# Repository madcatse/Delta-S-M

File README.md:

# Delta-S-M Ver.1.0 Gerber Files

Welcome to the first release of Gerber files for Delta-S-M Ver.1.0! This repository contains the manufacturing files necessary to produce the Delta-S-M Ver.1.0 board.

## Table of Contents
- [Introduction](#introduction)
- [Features](#features)
- [Getting Started](#getting-started)
- [Folder Structure](#folder-structure)
- [Cable pinout difference](#cable-pinout-difference)
- [Making SCART cable](#making-scart-cable)
- [License](#license)

## Introduction
Основной задачей данного проекта я поставил создание наиболее близкого к оригиналу клона персонального восьмибитного компьютера "Дельта-С", который в свою очередь является клоном ZX Spectrum 48K. Выбор модели был обусловлен давней мечтой об "улучшении" оригинальной машины, которой я обладаю с 1991 года. В процессе работы цель проекта несколько раз корректировалась и вместо точной копии стала некоторой "вариацией" на тему оригинала, с небольшими корректировками.

## Features
- High-performance microcontroller
- Multiple digital and analog I/O options
- Onboard peripherals such as LEDs, buttons, and connectors
- Expandable with additional modules or shields
- Compact form factor for easy integration

## Getting Started
To get started with Delta-S-M Ver.1.0, follow these steps:
1. Clone or download this repository.
2. Open the Gerber files in your preferred PCB manufacturing software.
3. Verify the design and make any necessary adjustments.
4. Generate the necessary manufacturing files (e.g., drill files, copper layers).
5. Submit the generated files to your preferred PCB manufacturer.
6. Review the manufacturer's guidelines and requirements for PCB production.
7. Proceed with the manufacturing process.
8. Once manufactured, assemble the components onto the PCB following the provided bill of materials (BOM).
9. Power up the Delta-S-M Ver.1.0 board and start exploring its capabilities!

## Folder Structure
The repository is organized as follows:
- /Gerber: Contains the Gerber files necessary for PCB manufacturing.
- /BOM: Includes the bill of materials (BOM) listing all components required for assembly.
- /Documentation: Provides additional documentation, schematics, and datasheets related to Delta-S-M Ver.1.0.

## Cable pinout difference

Be carefull, as there is a very important difference in video cable pinout between v0.1, v1.0 and v1.2 and up.

**v0.1 and v1.0 boards video pinout:**

- 1 - Sync
- 2 - Red
- 3 - N/C
- 4 - Blue
- 5 - Green
- 6 - GND
- 7 - +5V

**v1.2 boards video pinout:**

- 1 - Sync
- 2 - GND
- 3 - Red
- 4 - Green
- 5 - Blue
- 6 - Audio
- 7 - +5V

V1.2 boards are compatible with original Delta-S and Delta-128 and could be connected with their cables.

## Making SCART cable
The best video quality could be achived with SCART cable with RGB mode. Delta S-M is capable of outputting native RGB signal and uses a SCART cable to connect to RGB-capable TVs. The picture below illustrates pinout of both SCART plug and DIN-7 plug.

SCART Pinout

15 - Red
11 - Green
7 - Blue
20 - Sync
16 - ADD 180 Ohm resistor between computer and SCART plug and connect it to pin 16 to enable switching to correct RGB mode. Direct +5V could DAMAGE YOUR TV!
5, 9, 13, 17 and 21 (metal case) - Ground

## License
This project is licensed under the [MIT License](LICENSE). Feel free to use, modify, and distribute the Delta-S-M Ver.1.0 Gerber files as per the terms of the license.

For more details, refer to the [LICENSE](LICENSE) file.

---

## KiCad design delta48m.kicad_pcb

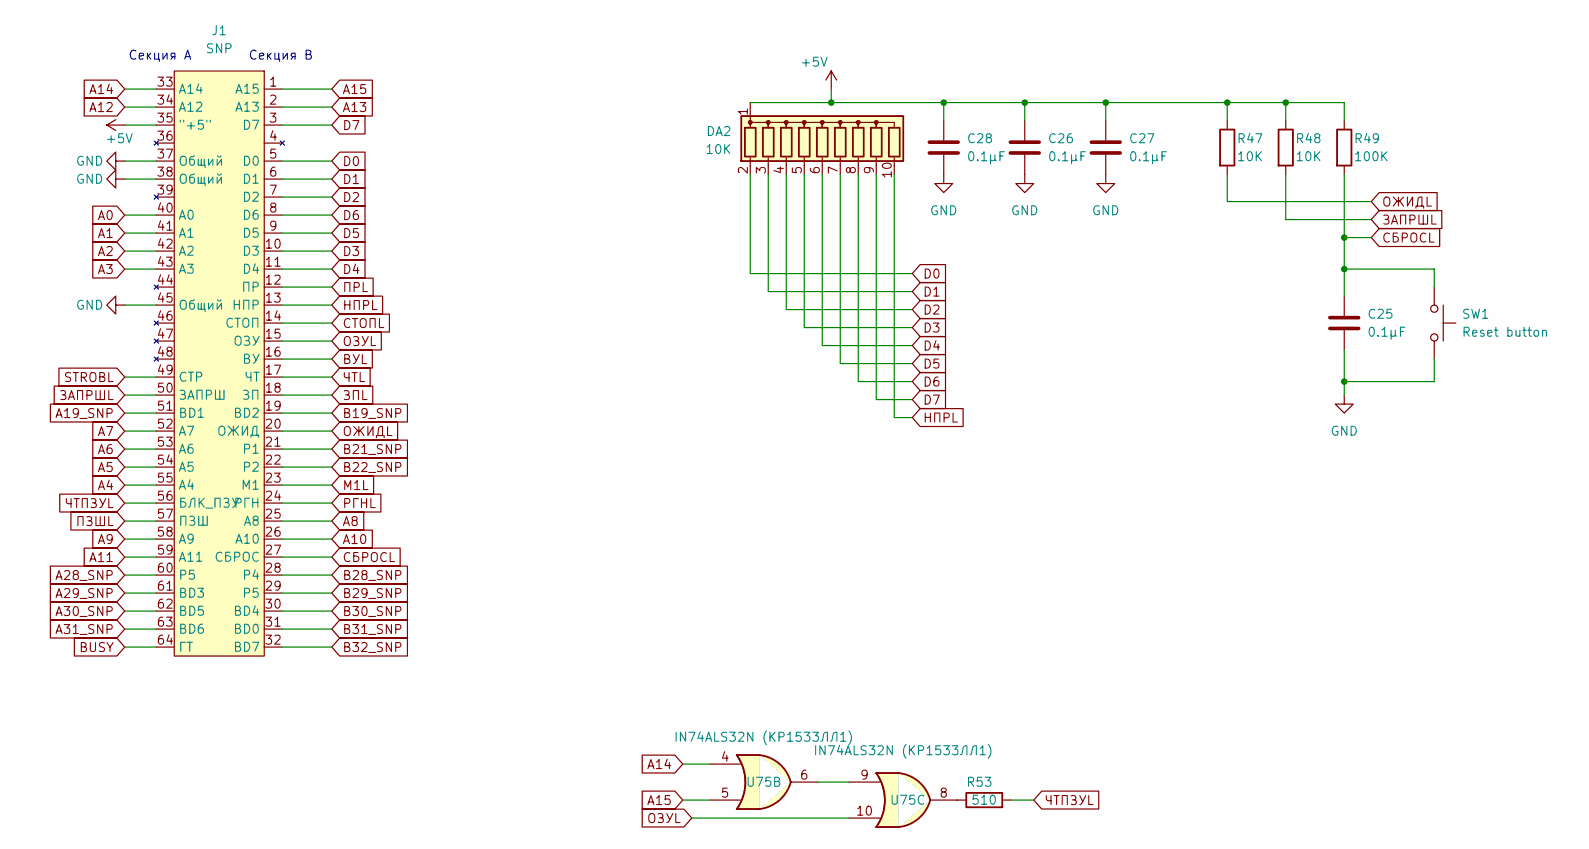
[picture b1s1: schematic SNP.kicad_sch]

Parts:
C25, C26, C27, C28: 0.1μF; C_Disc_D7.0mm_W2.5mm_P5.00mm
DA2: 10K; R_Array_SIP10
J1: SNP; snp59_96_female_angle_3
R47, R48: 10K; R_Axial_DIN0207_L6.3mm_D2.5mm_P10.16mm_Horizontal
R49: 100K; R_Axial_DIN0207_L6.3mm_D2.5mm_P10.16mm_Horizontal
R53: 510; R_Axial_DIN0207_L6.3mm_D2.5mm_P10.16mm_Horizontal
SW1: Reset button; SW_Tactile_SPST_Angled_PTS645Vx83-2LFS
U75: IN74ALS32N (КР1533ЛЛ1); DIP-14_W7.62mm_Socket

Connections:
+5V: C26.1, C27.1, C28.1, DA2.1 (common), J1.35 ("+5"), R47.1, R48.1, R49.1; also elsewhere on the board
A0: J1.40 (A0); also elsewhere on the board
A1: J1.41 (A1); also elsewhere on the board
A2: J1.42 (A2); also elsewhere on the board
A3: J1.43 (A3); also elsewhere on the board
A4: J1.55 (A4); also elsewhere on the board
A5: J1.54 (A5); also elsewhere on the board
A6: J1.53 (A6); also elsewhere on the board
A7: J1.52 (A7); also elsewhere on the board
A8: J1.25 (A8); also elsewhere on the board
A9: J1.58 (A9); also elsewhere on the board
A10: J1.26 (A10); also elsewhere on the board
A11: J1.59 (A11); also elsewhere on the board
A12: J1.34 (A12); also elsewhere on the board
A13: J1.2 (A13); also elsewhere on the board
A14: J1.33 (A14), U75.4; also elsewhere on the board
A15: J1.1 (A15), U75.5; also elsewhere on the board
A19_SNP: J1.51 (BD1); also elsewhere on the board
A28_SNP: J1.60 (P5); also elsewhere on the board
A29_SNP: J1.61 (BD3); also elsewhere on the board
A30_SNP: J1.62 (BD5); also elsewhere on the board
A31_SNP: J1.63 (BD6); also elsewhere on the board
B19_SNP: J1.19 (BD2); also elsewhere on the board
B21_SNP: J1.21 (P1); also elsewhere on the board
B22_SNP: J1.22 (P2); also elsewhere on the board
B28_SNP: J1.28 (P4); also elsewhere on the board
B29_SNP: J1.29 (P5); also elsewhere on the board
B30_SNP: J1.30 (BD4); also elsewhere on the board
B31_SNP: J1.31 (BD0); also elsewhere on the board
B32_SNP: J1.32 (BD7); also elsewhere on the board
BUSY: J1.64 (ГТ); also elsewhere on the board
D0: DA2.2 (R1), J1.5 (D0); also elsewhere on the board
D1: DA2.3 (R2), J1.6 (D1); also elsewhere on the board
D2: DA2.4 (R3), J1.7 (D2); also elsewhere on the board
D3: DA2.5 (R4), J1.10 (D3); also elsewhere on the board
D4: DA2.6 (R5), J1.11 (D4); also elsewhere on the board
D5: DA2.7 (R6), J1.9 (D5); also elsewhere on the board
D6: DA2.8 (R7), J1.8 (D6); also elsewhere on the board
D7: DA2.9 (R8), J1.3 (D7); also elsewhere on the board
GND: C25.2, C26.2, C27.2, C28.2, J1.37 (Общий), J1.38 (Общий), J1.45 (Общий), SW1.2; also elsewhere on the board
M1L: J1.23 (М1); also elsewhere on the board
unnamed: R53.1, U75.8
unnamed: U75.6, U75.9
STROBL: J1.49 (СТР); also elsewhere on the board
ВУL: J1.16 (ВУ); also elsewhere on the board
ЗАПРШL: J1.50 (ЗАПРШ), R48.2; also elsewhere on the board
ЗПL: J1.18 (ЗП); also elsewhere on the board
НПРL: DA2.10 (R9), J1.13 (НПР); also elsewhere on the board
ОЖИДL: J1.20 (ОЖИД), R47.2; also elsewhere on the board
ОЗУL: J1.15 (ОЗУ), U75.10; also elsewhere on the board
ПЗШL: J1.57 (ПЗШ); also elsewhere on the board
ПРL: J1.12 (ПР); also elsewhere on the board
РГНL: J1.24 (РГН); also elsewhere on the board
СБРОСL: C25.1, J1.27 (СБРОС), R49.2, SW1.1; also elsewhere on the board
СТОПL: J1.14 (СТОП); also elsewhere on the board
ЧТL: J1.17 (ЧТ); also elsewhere on the board
ЧТПЗУL: J1.56 (БЛК_ПЗУ), R53.2; also elsewhere on the board

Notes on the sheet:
Секция А
Секция В

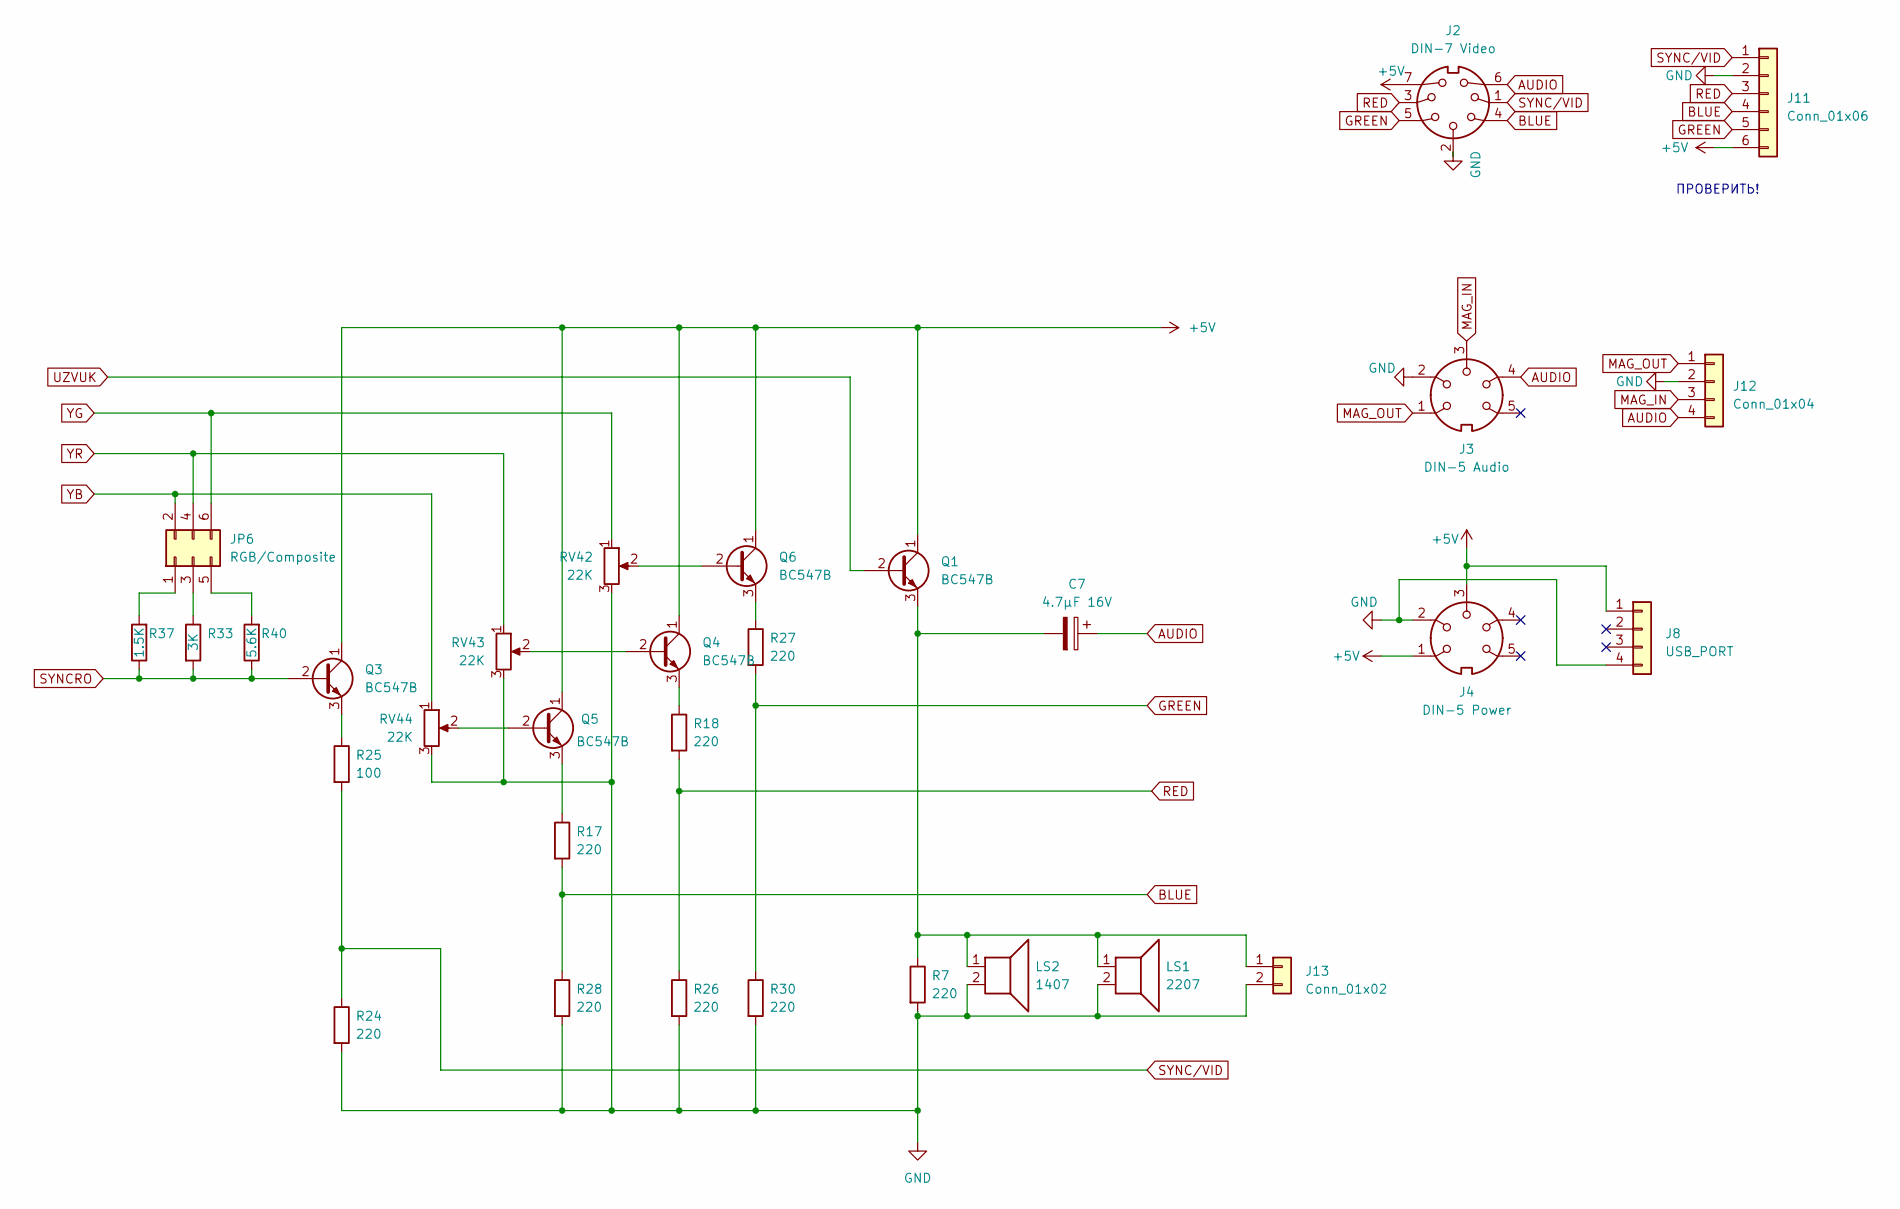
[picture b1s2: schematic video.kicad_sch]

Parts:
C7: 4.7µF 16V; CP_Radial_D4.0mm_P2.00mm
J2: DIN-7 Video; DIN-7-Variable
J3: DIN-5 Audio; DIN-5-Variable
J4: DIN-5 Power; DIN-5-Variable
J8: USB_PORT; USB-C Power board
J11: Conn_01x06; PinHeader_1x06_P2.54mm_Vertical
J12: Conn_01x04; PinHeader_1x04_P2.54mm_Vertical
J13: Conn_01x02; PinHeader_1x02_P2.54mm_Vertical
JP6: RGB/Composite; PinHeader_2x03_P2.54mm_Vertical
LS1: 2207; ZM-Piezo Buzzer-2207T2
LS2: 1407; 1407 Piezoelectric Passive Buzzer
Q1, Q3, Q4, Q5, Q6: BC547B; TO-92_Inline
R7, R17, R18, R24, R26, R27, R28, R30: 220; R_Axial_DIN0207_L6.3mm_D2.5mm_P10.16mm_Horizontal
R25: 100; R_Axial_DIN0207_L6.3mm_D2.5mm_P10.16mm_Horizontal
R33: 3K; R_Axial_DIN0207_L6.3mm_D2.5mm_P10.16mm_Horizontal
R37: 1.5K; R_Axial_DIN0207_L6.3mm_D2.5mm_P10.16mm_Horizontal
R40: 5.6K; R_Axial_DIN0207_L6.3mm_D2.5mm_P10.16mm_Horizontal
RV42, RV43, RV44: 22K; Potentiometer_Bourns_3299X_Horizontal

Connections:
+5V: J2.7, J4.1, J4.3, J8.1, J11.6, Q1.1 (C), Q3.1 (C), Q4.1 (C), Q5.1 (C), Q6.1 (C); also elsewhere on the board
AUDIO: C7.1, J2.6, J3.4, J12.4
BLUE: J2.4, J11.4, R17.2, R28.1
GND: J2.2, J3.2, J4.2, J8.4, J11.2, J12.2, J13.2, LS1.2, LS2.2, R7.2, R24.2, R26.2, R28.2, R30.2, RV42.3, RV43.3, RV44.3; also elsewhere on the board
GREEN: J2.5, J11.5, R27.2, R30.1
MAG_IN: J3.3, J12.3; also elsewhere on the board
MAG_OUT: J3.1, J12.1; also elsewhere on the board
unnamed: C7.2, J13.1, LS1.1, LS2.1, Q1.3 (E), R7.1
unnamed: JP6.1, R37.2
unnamed: JP6.3, R33.1
unnamed: JP6.5, R40.2
unnamed: Q3.3 (E), R25.1
unnamed: Q4.2 (B), RV43.2
unnamed: Q4.3 (E), R18.1
unnamed: Q5.2 (B), RV44.2
unnamed: Q5.3 (E), R17.1
unnamed: Q6.2 (B), RV42.2
unnamed: Q6.3 (E), R27.1
RED: J2.3, J11.3, R18.2, R26.1
SYNCRO: Q3.2 (B), R33.2, R37.1, R40.1; also elsewhere on the board
SYNC/VID: J2.1, J11.1, R24.1, R25.2
UZVUK: Q1.2 (B); also elsewhere on the board
YB: JP6.2, RV44.1; also elsewhere on the board
YG: JP6.6, RV42.1; also elsewhere on the board
YR: JP6.4, RV43.1; also elsewhere on the board

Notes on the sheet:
ПРОВЕРИТЬ!

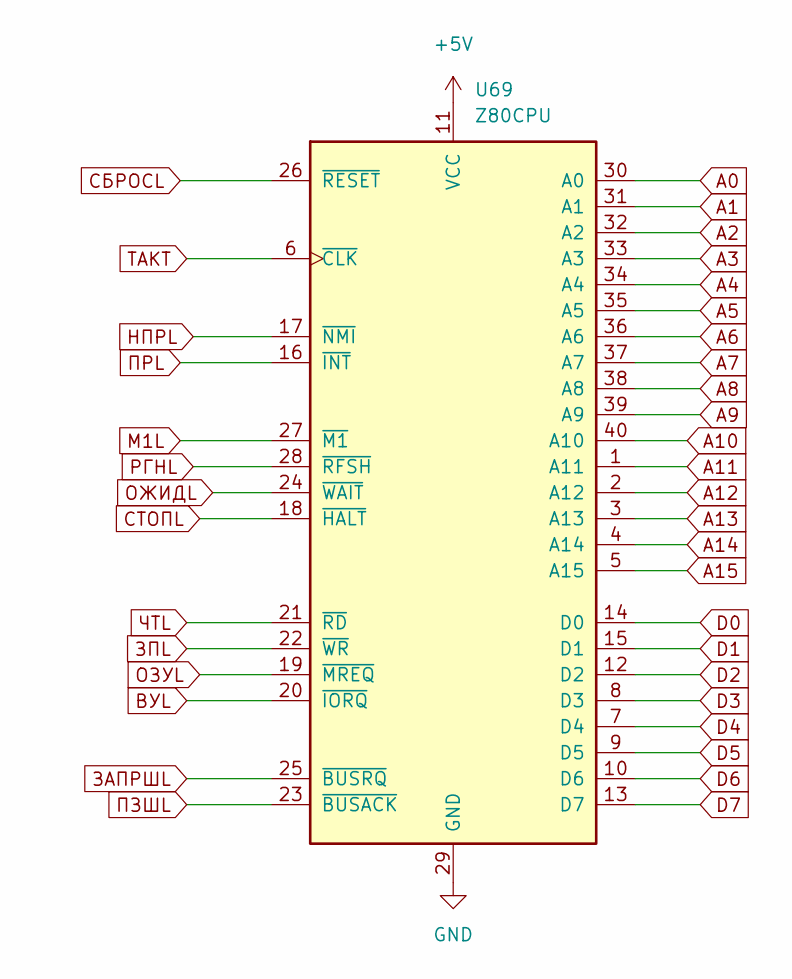
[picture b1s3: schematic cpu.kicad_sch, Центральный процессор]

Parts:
U69: Z80CPU; DIP-40_W15.24mm_Socket

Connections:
+5V: U69.11 (VCC); also elsewhere on the board
A0: U69.30 (A0); also elsewhere on the board
A1: U69.31 (A1); also elsewhere on the board
A2: U69.32 (A2); also elsewhere on the board
A3: U69.33 (A3); also elsewhere on the board
A4: U69.34 (A4); also elsewhere on the board
A5: U69.35 (A5); also elsewhere on the board
A6: U69.36 (A6); also elsewhere on the board
A7: U69.37 (A7); also elsewhere on the board
A8: U69.38 (A8); also elsewhere on the board
A9: U69.39 (A9); also elsewhere on the board
A10: U69.40 (A10); also elsewhere on the board
A11: U69.1 (A11); also elsewhere on the board
A12: U69.2 (A12); also elsewhere on the board
A13: U69.3 (A13); also elsewhere on the board
A14: U69.4 (A14); also elsewhere on the board
A15: U69.5 (A15); also elsewhere on the board
D0: U69.14 (D0); also elsewhere on the board
D1: U69.15 (D1); also elsewhere on the board
D2: U69.12 (D2); also elsewhere on the board
D3: U69.8 (D3); also elsewhere on the board
D4: U69.7 (D4); also elsewhere on the board
D5: U69.9 (D5); also elsewhere on the board
D6: U69.10 (D6); also elsewhere on the board
D7: U69.13 (D7); also elsewhere on the board
GND: U69.29 (GND); also elsewhere on the board
M1L: U69.27 (~M1); also elsewhere on the board
ВУL: U69.20 (~IORQ); also elsewhere on the board
ЗАПРШL: U69.25 (~BUSRQ); also elsewhere on the board
ЗПL: U69.22 (~WR); also elsewhere on the board
НПРL: U69.17 (~NMI); also elsewhere on the board
ОЖИДL: U69.24 (~WAIT); also elsewhere on the board
ОЗУL: U69.19 (~MREQ); also elsewhere on the board
ПЗШL: U69.23 (~BUSACK); also elsewhere on the board
ПРL: U69.16 (~INT); also elsewhere on the board
РГНL: U69.28 (~RFSH); also elsewhere on the board
СБРОСL: U69.26 (~RESET); also elsewhere on the board
СТОПL: U69.18 (~HALT); also elsewhere on the board
ТАКТ: U69.6 (~CLK); also elsewhere on the board
ЧТL: U69.21 (~RD); also elsewhere on the board

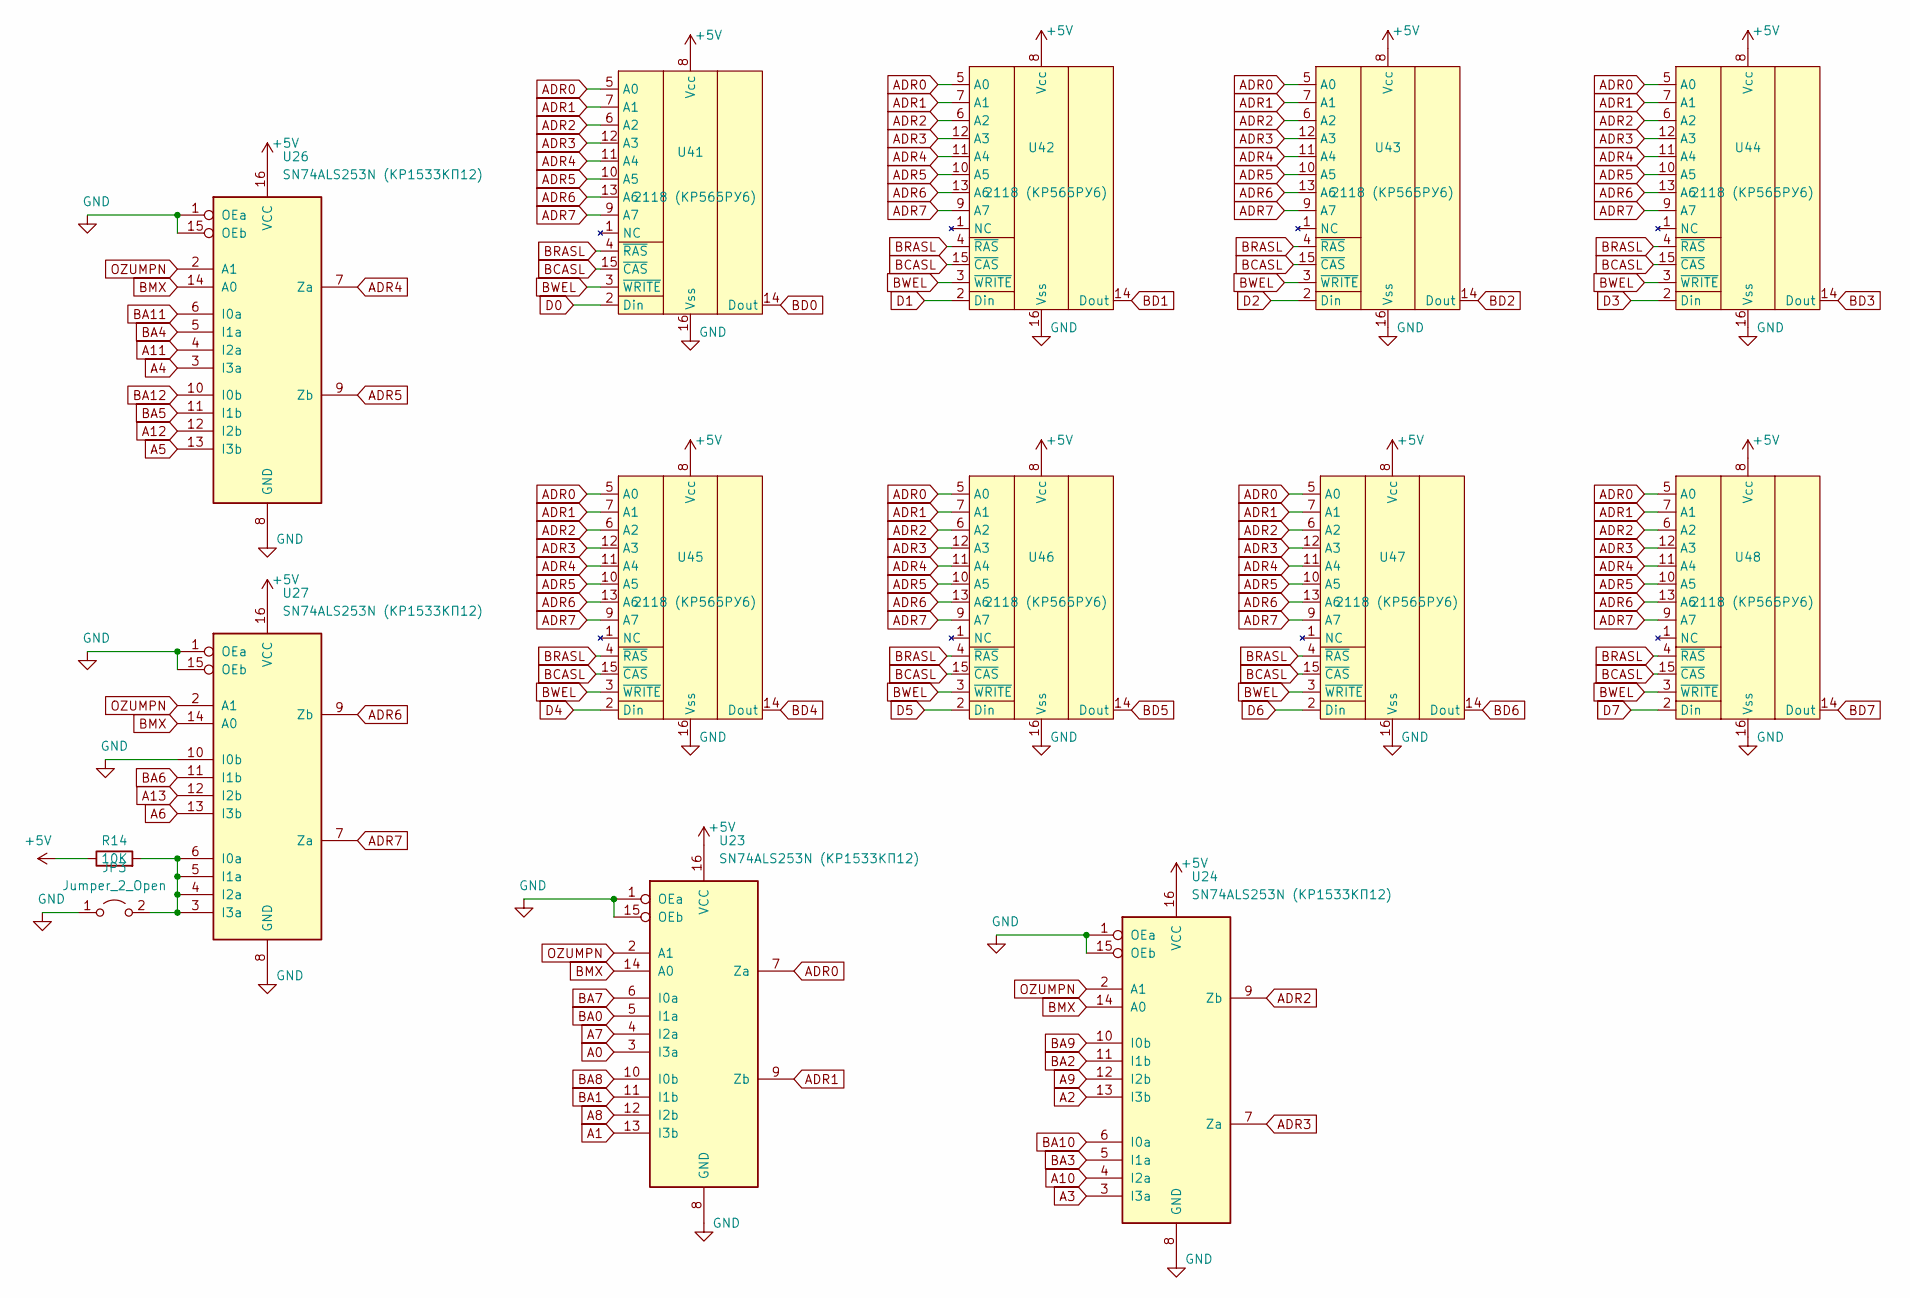
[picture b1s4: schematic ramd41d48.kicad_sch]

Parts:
JP3: Jumper_2_Open; PinHeader_1x02_P2.54mm_Vertical
R14: 10K; R_Axial_DIN0207_L6.3mm_D2.5mm_P10.16mm_Horizontal
U23, U24, U26, U27: SN74ALS253N (КР1533КП12); DIP-16_W7.62mm_Socket
U41, U42, U43, U44, U45, U46, U47, U48: 2118 (КР565РУ6); DIP-16_W7.62mm_Socket

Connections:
+5V: R14.1, U23.16 (VCC), U24.16 (VCC), U26.16 (VCC), U27.16 (VCC), U41.8 (Vcc), U42.8 (Vcc), U43.8 (Vcc), U44.8 (Vcc), U45.8 (Vcc), U46.8 (Vcc), U47.8 (Vcc), U48.8 (Vcc); also elsewhere on the board
A0: U23.3 (I3a); also elsewhere on the board
A1: U23.13 (I3b); also elsewhere on the board
A2: U24.13 (I3b); also elsewhere on the board
A3: U24.3 (I3a); also elsewhere on the board
A4: U26.3 (I3a); also elsewhere on the board
A5: U26.13 (I3b); also elsewhere on the board
A6: U27.13 (I3b); also elsewhere on the board
A7: U23.4 (I2a); also elsewhere on the board
A8: U23.12 (I2b); also elsewhere on the board
A9: U24.12 (I2b); also elsewhere on the board
A10: U24.4 (I2a); also elsewhere on the board
A11: U26.4 (I2a); also elsewhere on the board
A12: U26.12 (I2b); also elsewhere on the board
A13: U27.12 (I2b); also elsewhere on the board
ADR0: U23.7 (Za), U41.5 (A0), U42.5 (A0), U43.5 (A0), U44.5 (A0), U45.5 (A0), U46.5 (A0), U47.5 (A0), U48.5 (A0)
ADR1: U23.9 (Zb), U41.7 (A1), U42.7 (A1), U43.7 (A1), U44.7 (A1), U45.7 (A1), U46.7 (A1), U47.7 (A1), U48.7 (A1)
ADR2: U24.9 (Zb), U41.6 (A2), U42.6 (A2), U43.6 (A2), U44.6 (A2), U45.6 (A2), U46.6 (A2), U47.6 (A2), U48.6 (A2)
ADR3: U24.7 (Za), U41.12 (A3), U42.12 (A3), U43.12 (A3), U44.12 (A3), U45.12 (A3), U46.12 (A3), U47.12 (A3), U48.12 (A3)
ADR4: U26.7 (Za), U41.11 (A4), U42.11 (A4), U43.11 (A4), U44.11 (A4), U45.11 (A4), U46.11 (A4), U47.11 (A4), U48.11 (A4)
ADR5: U26.9 (Zb), U41.10 (A5), U42.10 (A5), U43.10 (A5), U44.10 (A5), U45.10 (A5), U46.10 (A5), U47.10 (A5), U48.10 (A5)
ADR6: U27.9 (Zb), U41.13 (A6), U42.13 (A6), U43.13 (A6), U44.13 (A6), U45.13 (A6), U46.13 (A6), U47.13 (A6), U48.13 (A6)
ADR7: U27.7 (Za), U41.9 (A7), U42.9 (A7), U43.9 (A7), U44.9 (A7), U45.9 (A7), U46.9 (A7), U47.9 (A7), U48.9 (A7)
BA0: U23.5 (I1a); also elsewhere on the board
BA1: U23.11 (I1b); also elsewhere on the board
BA2: U24.11 (I1b); also elsewhere on the board
BA3: U24.5 (I1a); also elsewhere on the board
BA4: U26.5 (I1a); also elsewhere on the board
BA5: U26.11 (I1b); also elsewhere on the board
BA6: U27.11 (I1b); also elsewhere on the board
BA7: U23.6 (I0a); also elsewhere on the board
BA8: U23.10 (I0b); also elsewhere on the board
BA9: U24.10 (I0b); also elsewhere on the board
BA10: U24.6 (I0a); also elsewhere on the board
BA11: U26.6 (I0a); also elsewhere on the board
BA12: U26.10 (I0b); also elsewhere on the board
BCASL: U41.15 (~CAS), U42.15 (~CAS), U43.15 (~CAS), U44.15 (~CAS), U45.15 (~CAS), U46.15 (~CAS), U47.15 (~CAS), U48.15 (~CAS); also elsewhere on the board
BD0: U41.14 (Dout); also elsewhere on the board
BD1: U42.14 (Dout); also elsewhere on the board
BD2: U43.14 (Dout); also elsewhere on the board
BD3: U44.14 (Dout); also elsewhere on the board
BD4: U45.14 (Dout); also elsewhere on the board
BD5: U46.14 (Dout); also elsewhere on the board
BD6: U47.14 (Dout); also elsewhere on the board
BD7: U48.14 (Dout); also elsewhere on the board
BMX: U23.14 (A0), U24.14 (A0), U26.14 (A0), U27.14 (A0); also elsewhere on the board
BRASL: U41.4 (~RAS), U42.4 (~RAS), U43.4 (~RAS), U44.4 (~RAS), U45.4 (~RAS), U46.4 (~RAS), U47.4 (~RAS), U48.4 (~RAS); also elsewhere on the board
BWEL: U41.3 (~WRITE), U42.3 (~WRITE), U43.3 (~WRITE), U44.3 (~WRITE), U45.3 (~WRITE), U46.3 (~WRITE), U47.3 (~WRITE), U48.3 (~WRITE); also elsewhere on the board
D0: U41.2 (Din); also elsewhere on the board
D1: U42.2 (Din); also elsewhere on the board
D2: U43.2 (Din); also elsewhere on the board
D3: U44.2 (Din); also elsewhere on the board
D4: U45.2 (Din); also elsewhere on the board
D5: U46.2 (Din); also elsewhere on the board
D6: U47.2 (Din); also elsewhere on the board
D7: U48.2 (Din); also elsewhere on the board
GND: JP3.1 (A), U23.1 (OEa), U23.8 (GND), U23.15 (OEb), U24.1 (OEa), U24.8 (GND), U24.15 (OEb), U26.1 (OEa), U26.8 (GND), U26.15 (OEb), U27.1 (OEa), U27.8 (GND), U27.10 (I0b), U27.15 (OEb), U41.16 (Vss), U42.16 (Vss), U43.16 (Vss), U44.16 (Vss), U45.16 (Vss), U46.16 (Vss), U47.16 (Vss), U48.16 (Vss); also elsewhere on the board
unnamed: JP3.2 (B), R14.2, U27.3 (I3a), U27.4 (I2a), U27.5 (I1a), U27.6 (I0a)
OZUMPN: U23.2 (A1), U24.2 (A1), U26.2 (A1), U27.2 (A1); also elsewhere on the board

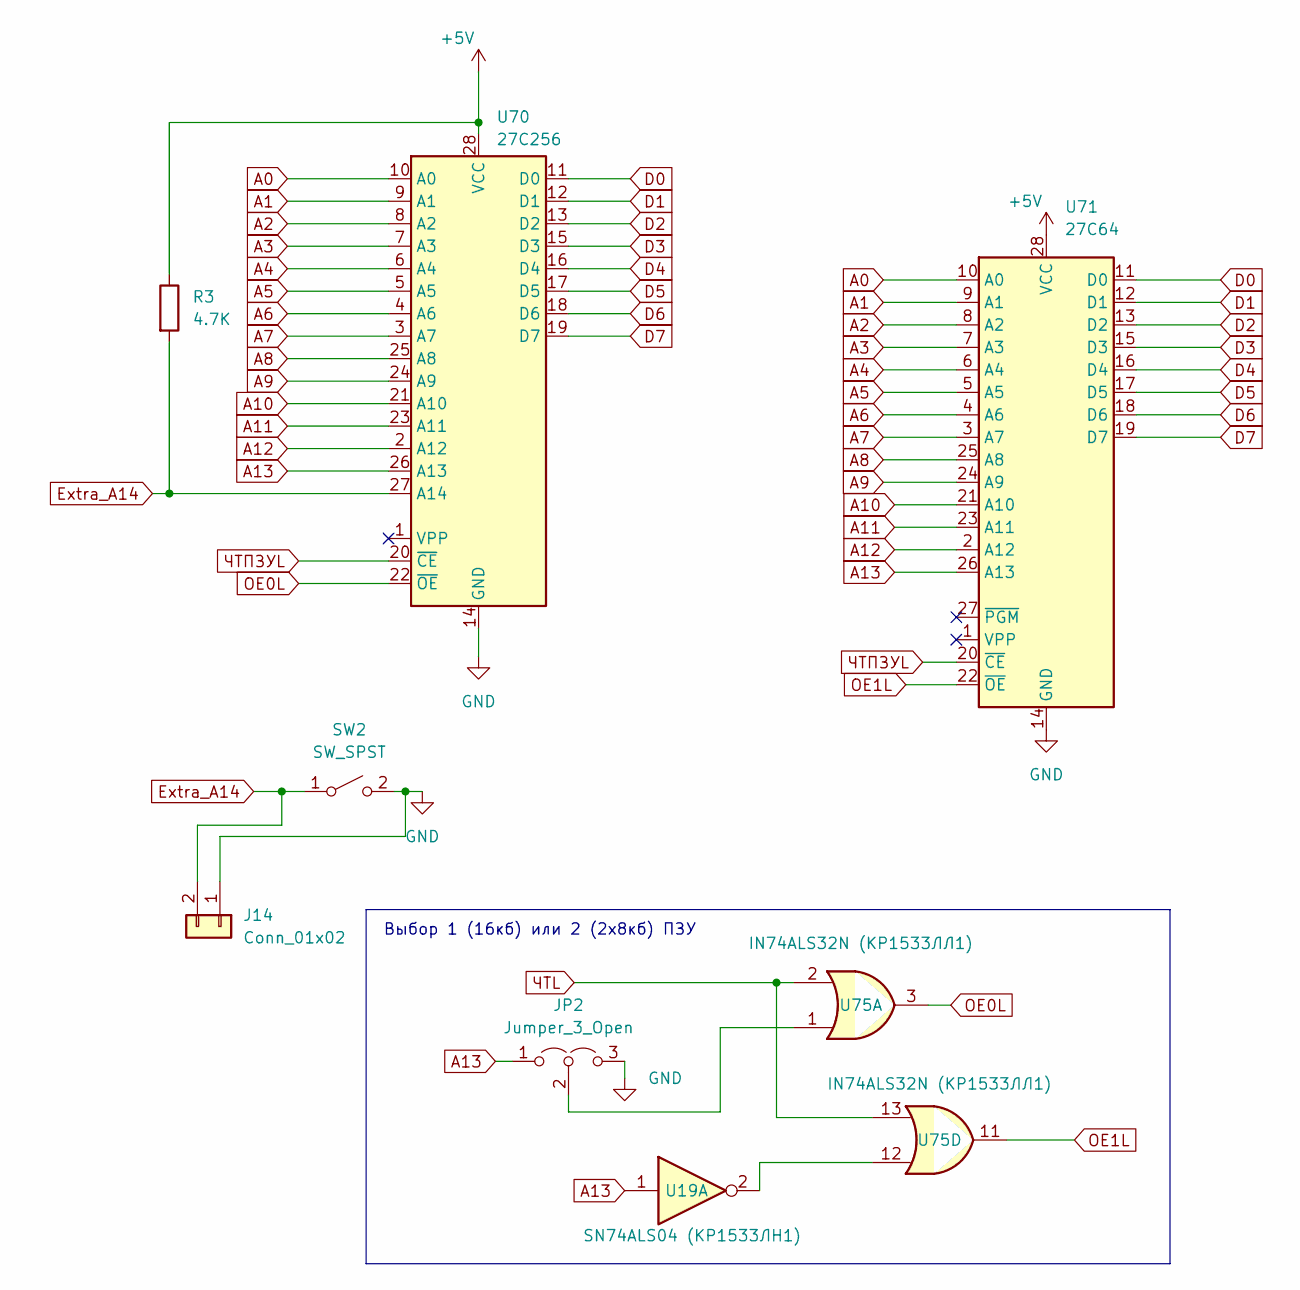
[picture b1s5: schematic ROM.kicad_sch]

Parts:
J14: Conn_01x02; PinHeader_1x02_P2.54mm_Vertical
JP2: Jumper_3_Open; PinHeader_1x03_P2.54mm_Vertical
R3: 4.7K; R_Axial_DIN0207_L6.3mm_D2.5mm_P10.16mm_Horizontal
SW2: SW_SPST; onoffswitch
U19: SN74ALS04 (КР1533ЛН1); DIP-14_W7.62mm_Socket
U70: 27C256; DIP-28_W15.24mm_Socket
U71: 27C64; DIP-28_W15.24mm_Socket
U75: IN74ALS32N (КР1533ЛЛ1); DIP-14_W7.62mm_Socket

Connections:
+5V: R3.1, U70.28 (VCC), U71.28 (VCC); also elsewhere on the board
A0: U70.10 (A0), U71.10 (A0); also elsewhere on the board
A1: U70.9 (A1), U71.9 (A1); also elsewhere on the board
A2: U70.8 (A2), U71.8 (A2); also elsewhere on the board
A3: U70.7 (A3), U71.7 (A3); also elsewhere on the board
A4: U70.6 (A4), U71.6 (A4); also elsewhere on the board
A5: U70.5 (A5), U71.5 (A5); also elsewhere on the board
A6: U70.4 (A6), U71.4 (A6); also elsewhere on the board
A7: U70.3 (A7), U71.3 (A7); also elsewhere on the board
A8: U70.25 (A8), U71.25 (A8); also elsewhere on the board
A9: U70.24 (A9), U71.24 (A9); also elsewhere on the board
A10: U70.21 (A10), U71.21 (A10); also elsewhere on the board
A11: U70.23 (A11), U71.23 (A11); also elsewhere on the board
A12: U70.2 (A12), U71.2 (A12); also elsewhere on the board
A13: JP2.1 (A), U19.1, U70.26 (A13), U71.26 (A13); also elsewhere on the board
D0: U70.11 (D0), U71.11 (D0); also elsewhere on the board
D1: U70.12 (D1), U71.12 (D1); also elsewhere on the board
D2: U70.13 (D2), U71.13 (D2); also elsewhere on the board
D3: U70.15 (D3), U71.15 (D3); also elsewhere on the board
D4: U70.16 (D4), U71.16 (D4); also elsewhere on the board
D5: U70.17 (D5), U71.17 (D5); also elsewhere on the board
D6: U70.18 (D6), U71.18 (D6); also elsewhere on the board
D7: U70.19 (D7), U71.19 (D7); also elsewhere on the board
Extra_A14: J14.2, R3.2, SW2.1 (A), U70.27 (A14)
GND: J14.1, JP2.3 (B), SW2.2 (B), U70.14 (GND), U71.14 (GND); also elsewhere on the board
unnamed: JP2.2 (C), U75.1
unnamed: U19.2, U75.12
OE0L: U70.22 (~OE), U75.3
OE1L: U71.22 (~OE), U75.11
ЧТL: U75.2, U75.13; also elsewhere on the board
ЧТПЗУL: U70.20 (~CE), U71.20 (~CE); also elsewhere on the board

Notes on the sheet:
Выбор 1 (16кб) или 2 (2х8кб) ПЗУ
